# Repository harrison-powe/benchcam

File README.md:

# BenchCam

catching actuators in the act

BenchCam is a **local-first**, bench-side **capture + event-marking workflow**
for documenting hardware work. You start a session, log time-stamped markers as
you work (e.g. "power on", "chip lifted", "fault"), optionally record video with
an **off-the-shelf webcam**, and end up with a self-contained folder of plain
files you can read with any text editor — plus an optional auto-edited review
clip that timelapses the boring parts and slows down around each marker.

> **Status:** v0, now exercised on **real bench sessions**. Two real
> `hello-motion` sessions exist — a connection-debugging session and one where the
> actuator was recorded **spinning on command** (open-loop bring-up, narrated on
> camera). The capture path, the physical **START/MARK/STOP/MUTE** buttons with
> their record/mute LEDs and OLED status panel, and the full post-capture pipeline
> (transcribe → auto-chapter → speech-aware review clip) have all run on real
> footage. Honest caveats: the physical controls still run on the **breadboard**
> rig — a v1 control PCB is built and electrically verified but has **never
> successfully driven anything**
> (see [The v1 control PCB](#the-v1-control-pcb-built-and-verified-not-yet-working)) —
> the actuator sessions were bring-up/debugging rather than a polished showcase,
> and raw capture still records to a **microSD** until the external SSD is
> deployed. Treat it as an early, working tool, not a finished product.

## What BenchCam is (and is not)

- It is a **software workflow**: it records a session, logs markers (events with
  a timestamp + label), and can auto-edit a review clip. Everything is kept in
  local files only — **no cloud sync, no accounts**.
- For video it drives **existing, off-the-shelf tools**: an `ffmpeg` subprocess
  capturing a USB webcam, or OBS Studio over OBS WebSocket. **BenchCam does not
  build, sell, or include any camera, capture card, or hardware** — you supply a
  regular webcam and (optionally) OBS or ffmpeg.
- It is **not** a camera system and **not** a robotics or motion-control system.
  It uses off-the-shelf cameras and compute (a USB webcam, a Raspberry Pi) and
  does **not** build a camera, capture card, image sensor, or high-speed video
  electronics. It **does** have physical controls — tactile START/MARK/STOP/MUTE
  buttons, record/mute status LEDs, and a small I²C status display wired to the
  Pi's GPIO — and it switches **one bench ring light** (an illumination load, through
  a low-side MOSFET) so the light follows the recording. That is the entire extent
  of what it drives: it stays on the **observation** side and **never commands
  actuators or any moving hardware** (it may *receive* external marker events, but
  never commands motion).

v0 ships with a **NullRecorder** (records no video) so you can use and test the
session + marker workflow immediately, with or without a camera. The
**FfmpegRecorder** records real, audio-synced video by driving an external
`ffmpeg`: on **Linux / Raspberry Pi** it captures the webcam over V4L2 and the mic
over ALSA into `capture.mkv` — this is the primary bench setup — and on
**Windows** it captures over DirectShow (see
[Recording video with ffmpeg](#recording-video-with-ffmpeg)). The **ObsRecorder**
drives OBS Studio's recording on Windows (see
[Recording video with OBS](#recording-video-with-obs)).

## How it's deployed (two machines)

In the real bench setup the work is split across two machines:

- **Capture appliance — Raspberry Pi 5 (Linux).** The camera, ring light, and mic
  live at the bench on the Pi. It records over V4L2/ALSA, exposes the physical
  GPIO controls, and runs the dashboard and the button daemon as always-on
  `systemd` services (both survive reboot). Marking a session never needs the
  laptop.
- **Compute / edit / upload — Windows laptop.** Whisper transcription, silero-VAD,
  the `edit` render, and the Claude `label`/`autochapter` API calls run here (on
  the GPU). `benchcam fetch <id>` pulls a session off the Pi over `scp`; only the
  small finished `review.mp4` is uploaded.

The heavy, torch-based extras (`[transcribe]`, `[vad]`) and the `[label]` extra are
**laptop-only** — the Pi install stays stdlib-only so capture has no heavy deps.

### Physical controls (GPIO)

Four tactile buttons, two status LEDs, an I²C status display, and one switched
bench light wire to the Pi's 40-pin header (3.3V logic only):

| Function | GPIO | What it does |
| --- | --- | --- |
| **START** | 27 | create a session and start recording |
| **MARK** | 17 | drop a frame-accurate `source=gpio` marker |
| **STOP** | 22 | stop recording and end the session |
| **MUTE** | 23 | toggle a mute span (force-timelapsed out of the review) |
| record LED | 5 | lit while a session is RUNNING |
| mute LED | 24 | lit while a mute span is open |
| ring light | 6 | bench light through an IRLZ44N low-side MOSFET; on while RUNNING |
| OLED | I²C-1 | SSD1306 128×64 at `0x3C`: elapsed, marker count, mute badge, free space |

The Pi-local daemon [gpio_buttons.py](gpio_buttons.py) debounces the presses and
calls the same session/marker code the CLI uses, so button-driven and CLI-driven
sessions are cross-process safe. It runs as the always-on `benchcam-buttons`
service. Everything below is validated on the **breadboard** rig:

- The **record LED** is derived from the on-disk session state rather than
  in-memory state, so it stays correct across a daemon restart.
- The **status display** shows elapsed time, marker count, a mute badge, and free
  space with a low-space flag — measured against the same pre-flight floor the
  recorder enforces, so the panel can never show a healthy number while START
  would refuse. It refreshes on a background thread, fails soft (no display fault
  can affect capture), and retries a lost panel every 30s.
- **SIGTERM/SIGINT** clears both LEDs and the panel, so a stopped daemon never
  leaves a lit record light or a frozen `●REC` frame on the bench.
- **Mute spans survive a daemon restart** via a session-local sidecar
  (`mute_open.json`) that holds only the currently-open span. `mute_spans.csv`
  itself stays append-only and complete-rows-only, so the renderer never sees a
  half-written span and mistakes it for one running to end-of-session.
- The **ring light** follows the recording through the MOSFET. The circuit is
  validated, but the light currently on the bench has a capacitive touch switch
  that resets on power loss — so the MOSFET can turn it off and never back on.
  Blocked on swapping in a light with a mechanical switch, not on hardware or code.

### The v1 control PCB (built and verified, not yet working)

A single-sided control board was designed and CNC-milled in-house from the KiCad
project in [control-board/](control-board/): 100 × 80 mm FR-1, four buttons,
record/mute LEDs, a 4-pin I²C header for the OLED, an IRLZ44N low-side MOSFET on
a screw terminal for the bench light, and a 2×20 IDC ribbon to the Pi header.
Designed 2026-07-18, milled 07-19, continuity-verified 07-26, fully soldered and
metered 08-02. Because it was milled rather than fabbed, the gerbers and mill
gcode are tracked alongside the design as the reproduction record.

**It has never successfully driven anything.** First bring-up crashed the Pi
twice, and a J1 ground path is intermittent; diagnosis is ongoing. The
**breadboard rig remains the live control surface** for every session.

As-built deltas, recorded so future debugging doesn't chase them:

- **R3 is 220Ω on the board, not the 150Ω in the schematic** (MOSFET gate series
  resistor). The schematic deliberately keeps the designed value.
- A deliberate **solder bridge spans R3 pad 2 to R4 pad 1** — both are already on
  the gate net; it repairs a trace broken during rework. It is a repair, not a
  design change, and a re-mill would not reproduce it.
- **Only the J1 pins that carry a net are soldered** (21 of 40); the other 19 are
  unconnected in the netlist.

## Requirements

- **Python 3.11 or newer** (developed and validated on Python 3.13). The core is
  pure standard library — no third-party packages are required to install or run
  the session/marker workflow or the dashboard.
- For video recording: a working `ffmpeg` binary on your `PATH` (only needed if
  you use `--recorder ffmpeg`; the default `null` recorder needs nothing extra).
- For the OBS recorder: OBS Studio 28+ and the optional `benchcam[obs]` extra
  (only needed if you use `--recorder obs`). See
  [Recording video with OBS](#recording-video-with-obs).
- A regular **USB webcam** if you want video (BenchCam does not provide one).

## Install (Windows / laptop)

The steps below set up the **laptop** (editing, transcription, upload). The
**Raspberry Pi capture box** uses the same editable install on Linux (`pip install
-e .`, no heavy extras) — see
[Recording headless on a Raspberry Pi](#3-recording-headless-on-a-raspberry-pi-linux--v4l2--alsa)
for the capture side.

Open **PowerShell** (or **Command Prompt**) in the project folder.

```powershell
# 1. Create and activate a virtual environment
py -3.11 -m venv .venv
.\.venv\Scripts\Activate.ps1

# 2. Install BenchCam (editable)
pip install -e .
```

If PowerShell blocks the activation script, allow it for the current user:

```powershell
Set-ExecutionPolicy -Scope CurrentUser -ExecutionPolicy RemoteSigned
```

You can also run BenchCam without installing the console script:

```powershell
python -m benchcam --help
```

## Usage (Windows v0)

A session is just four commands. Run them from the same folder so they share the
same `sessions\` directory.

```powershell
# Create a new session (uses the NullRecorder by default)
benchcam new --profile bench-a

# Start the session clock
benchcam run

# Log markers as you work (quote labels that contain spaces)
benchcam mark "power on"
benchcam mark "chip lifted"
benchcam mark "fault observed"

# Close the session
benchcam end
```

### Where sessions are stored

By default session folders are created under `.\sessions\` in the current
directory. To put **all** session data (markers and collected videos) somewhere
else — for example an external SSD — set the `BENCHCAM_SESSIONS_ROOT`
environment variable. Every command honors it, so new sessions and the videos
collected into them land there with no code change and no per-command flag:

```powershell
# Persist it for your user (new shells pick it up automatically):
setx BENCHCAM_SESSIONS_ROOT "E:\benchcam-sessions"

# ...or just for the current shell:
$env:BENCHCAM_SESSIONS_ROOT = "E:\benchcam-sessions"
```

An explicit `--sessions-root PATH` on any command overrides the env var, which
overrides the `.\sessions\` default. No drive letter is hardcoded — point it at
whatever drive you like (the external SSD is the intended home once it's
available).

### Fast marking with `benchcam live`

`new`/`run`/`mark`/`end` each run as a separate process, which is fine for
occasional marks but slow when your hands are busy at the bench. `benchcam live`
opens a single long-running shell that holds the active session in memory and
marks on **one keypress** — no per-mark process startup, no re-reading
`markers.csv`.

```powershell
# Create a session first (if you don't already have an active one)
benchcam new --profile bench-a

# Enter the live shell (starts the session if it hasn't started yet)
benchcam live
```

Inside the shell:

| Key | Action |
| --- | --- |
| `Space` / `Enter` | Mark **now**, no label. Fast path — prints index + elapsed seconds instantly. |
| `l` | Mark now, then type a one-line label (empty label is allowed). |
| `n` | Append a line to `notes.md` (fills the gap where notes were write-once). |
| `s` | Show status: session id, elapsed time, marker count so far. |
| `q` | Quit cleanly: stop the recorder, end the session, print a summary. |

Notes:

- `live` attaches to the same active session as the other commands. If the
  session is still `created`, it starts it (same effect as `run`, including
  `recorder.start`). If it has already `ended`, it refuses with a clear message.
- Every mark is still **appended to `markers.csv` immediately** for crash
  safety; only the next marker index is tracked in memory.
- Markers made here use `source = manual`, exactly like `benchcam mark`.

This produces a folder like:

```
sessions\2026-06-17_05-43-00\
    session.json
    markers.csv
    notes.md
```

### session.json

```json
{
  "session_id": "2026-06-17_05-43-00",
  "created_wall_time": "2026-06-17T05:43:00.123456+00:00",
  "profile": "bench-a",
  "camera": "",
  "microphone": "",
  "recorder": "null",
  "storage_path": "sessions\\2026-06-17_05-43-00",
  "notes": "",
  "status": "ended",
  "started_wall_time": "2026-06-17T05:43:10.000000+00:00",
  "ended_wall_time": "2026-06-17T05:45:00.000000+00:00"
}
```

### markers.csv

```csv
marker_index,elapsed_seconds,wall_time,source,label,narration
1,2.500,2026-06-17T05:43:12.500000+00:00,gpio,Power Connected,so I've got power to the board now
2,15.250,2026-06-17T05:43:25.250000+00:00,manual,chip lifted,
```

- `elapsed_seconds` is measured from when the session started (`benchcam run`).
- `source` records where the marker came from: `manual` (`benchcam mark` or the
  dashboard), `gpio` (a physical button press), or `auto` (proposed by
  `benchcam autochapter`). `gpio`/`manual` are ground truth and win over `auto`
  on conflict.
- `label` is the short on-screen chapter title. `narration` is the raw
  transcribed speech near the marker (written by `benchcam transcribe`), kept in
  its own column so transcription and labeling never clobber each other.

### notes.md

A free-form Markdown file for whatever you want to jot down during the session.

## CLI reference

| Command | What it does |
| --- | --- |
| `benchcam new` | Create a new session folder and make it the active session. |
| `benchcam run` | Start recording / start the session clock. |
| `benchcam mark "label"` | Append a time-stamped marker to the active session. |
| `benchcam live` | Interactive shell that marks the active session on a single keypress. |
| `benchcam end` | Stop recording and close the active session. |
| `benchcam transcribe` | Fill each marker's `narration` from the audio with Whisper *(laptop; `[transcribe]` extra)*. |
| `benchcam label` | Summarize each marker's narration into a terse technical `label` via the Claude API *(laptop; `[label]` extra + `$ANTHROPIC_API_KEY`)*. |
| `benchcam autochapter` | Propose chapters from the **full-session** transcript and write them as `source=auto` markers; merges with real markers, which win *(laptop; `[transcribe]`+`[label]`)*. |
| `benchcam chapters` | Review/re-title chapters without re-watching: print, or `--edit`/`--apply` an editable `chapters.txt` (updates only the `label` column). |
| `benchcam edit` | Render a marker-aware `review.mp4` (timelapse + normal-speed windows + persistent chapter tags). Flags: `--vad`, `--auto`, `--preview`, `--fetch`. |
| `benchcam publish` | Export a paste-ready YouTube chapter block (remapped review timestamps) to `youtube_chapters.txt`. Read-only; never uploads. |
| `benchcam fetch` | Pull a recorded session off the Pi over `scp` to the laptop and open it *(run on the laptop)*. |
| `benchcam dashboard` | Local web UI to run a whole session (start/mark/stop/review) from a browser. |

Useful options:

- `benchcam new --profile NAME --camera DESC --microphone DESC --recorder {null,obs,ffmpeg} --notes "..."`
- `benchcam mark "label" --source external`
- `benchcam edit --session ID --pre 3 --post 5 --speed 30 [--vad] [--auto] [--preview] [--fetch] --font PATH`
- `--sessions-root PATH` (on any command) to use a different sessions directory.

Roughly, a full session flows: **capture** (Pi: `run`/`mark`/`end` or the GPIO
buttons) → **fetch** to the laptop → **transcribe** + **label** *or* **autochapter**
→ **edit** → optionally **chapters** to re-title → **publish** the chapter block.
`benchcam edit --auto` runs the transcribe → autochapter → render chain in one
command, skipping any step whose output already exists.

The "active" session is tracked by a small pointer file at
`sessions\.active`, so `run`, `mark`, and `end` know which session to use.

## Recorders

- **NullRecorder** (`null`, default): records no video. Lets you exercise the
  session and marker workflow, and pairs well with capturing video manually in a
  separate app.
- **ObsRecorder** (`obs`): drives OBS Studio's recording over OBS WebSocket v5
  (optional `benchcam[obs]` extra). See
  [Recording video with OBS](#recording-video-with-obs).
- **FfmpegRecorder** (`ffmpeg`): records one capture file per session by driving
  an external `ffmpeg` binary. Two paths are supported and selected by platform:
  Windows (DirectShow / dshow, video-only `capture.mp4`) and Linux (V4L2 + ALSA,
  `capture.mkv` with audio — e.g. a Raspberry Pi capturing from a C920). See
  [Recording video with ffmpeg](#recording-video-with-ffmpeg).

See `src/benchcam/recorders/` for the recorder code.

## Recording video with ffmpeg

The `ffmpeg` recorder captures one file into the session folder (**`capture.mp4`**
on Windows, **`capture.mkv`** on Linux). It starts when the session starts, so the
video timecode lines up with each marker's `elapsed_seconds`. ffmpeg is run as an
external binary — BenchCam adds no Python ffmpeg dependency, so you must have
`ffmpeg` on your `PATH` (`winget install Gyan.FFmpeg`, or download from
[ffmpeg.org](https://ffmpeg.org/download.html) and add it to `PATH`; on Debian/RPi
OS `sudo apt install ffmpeg`).

### 1. Find your camera's device name

The DirectShow device name (for a Logitech C920S it is usually
`HD Pro Webcam C920S`) must be passed exactly. List the devices on your machine:

```powershell
ffmpeg -list_devices true -f dshow -i dummy
```

Look under "DirectShow video devices" for the quoted name of your webcam.

### 2. Start a session that records from the camera

Pass the device name with `--camera`; it is stored in `session.json` and used as
the source of truth for the device. (You can also set the `BENCHCAM_CAMERA`
environment variable; an explicit `--camera` on the session wins.)

```powershell
benchcam new --recorder ffmpeg --camera "HD Pro Webcam C920S" --profile bench-a
benchcam live
```

`benchcam live` (or `benchcam run`) launches ffmpeg in the background and returns
immediately; quitting `live` (or `benchcam end`) sends `q` to ffmpeg so the MP4
is finalized and playable, force-killing only if it does not exit in time. If
`ffmpeg` is missing from `PATH`, or no camera name is configured, the command
fails with a clear message instead of silently recording nothing.

Defaults are tuned for the C920S: 1080p30 over MJPEG, H.264 (`libx264`), video
only (no audio). An `ffmpeg.log` is written next to the video for troubleshooting.

### 3. Recording headless on a Raspberry Pi (Linux / V4L2 + ALSA)

On Linux the recorder captures over **V4L2** and writes **`capture.mkv`**. The
C920 emits MJPEG natively, so the stream is **copied** (`-c:v copy`) — the Pi
never transcodes — and Matroska is used because MJPEG stream-copy is unreliable
in `.mp4`. ALSA audio (e.g. a Yeti Nano) is muxed into the same file.

The defaults match a confirmed C920 + Yeti Nano setup, so a plain session works
out of the box:

```bash
benchcam new --recorder ffmpeg --profile bench-pi
benchcam run        # captures /dev/video0 (mjpeg 1920x1080@30) + Yeti via ALSA
# ... benchcam mark "label" ...
benchcam end        # sends 'q' so capture.mkv is finalized
```

Everything is configurable (nothing is hardcoded in the command builder):

| Setting        | Default                   | Override |
| -------------- | ------------------------- | -------- |
| Video device   | `/dev/video0`             | `--camera` (stored in session.json) or `BENCHCAM_CAMERA` |
| Audio device   | `plughw:CARD=Nano,DEV=0`  | `--microphone` (stored in session.json) or `BENCHCAM_MICROPHONE` (set empty to disable audio) |
| Input format   | `mjpeg`                   | `BENCHCAM_INPUT_FORMAT` |
| Resolution     | `1920x1080`               | `BENCHCAM_VIDEO_SIZE` (`WxH`) |
| Frame rate     | `30`                      | `BENCHCAM_FRAMERATE` |

Discover V4L2 devices with `v4l2-ctl --list-devices` and ALSA capture devices
with `arecord -L`. The underlying command is equivalent to the manually
validated:

```bash
ffmpeg -f v4l2 -input_format mjpeg -framerate 30 -video_size 1920x1080 \
  -i /dev/video0 -f alsa -ac 2 -ar 44100 -i plughw:CARD=Nano,DEV=0 \
  -c:v copy -c:a aac capture.mkv
```

> Harmless `Dequeued v4l2 buffer contains corrupted data` warnings at stream
> startup are expected; they are logged to `ffmpeg.log` and are not fatal.

> macOS note: the avfoundation input path is still a TODO stub in
> `build_ffmpeg_command`.

## Recording video with OBS

The `obs` recorder lets BenchCam drive **OBS Studio**'s recording over OBS
WebSocket v5. OBS stays your live dashboard (preview, framing, focus) while
BenchCam tells it when to start and stop. Because BenchCam triggers the start,
marker `elapsed_seconds` lines up with the OBS video timecode automatically.

**OBS writes the video to its own configured recording folder** (BenchCam can't
change where OBS records). So when the session ends, BenchCam **collects** that
video — it *moves* the file into the session folder as `capture.<ext>` (the
extension is whatever OBS wrote, `.mkv` or `.mp4`), so the video ends up right
next to `markers.csv` / `session.json` / `notes.md` and each session folder is
self-contained. The `obs_recording.txt` pointer and a `notes.md` line are updated
to the new in-folder path.

If the move can't happen (file still locked, drive missing, etc.), the session
still ends cleanly and the pointer keeps the original OBS path — collection
degrades to "pointer to the external file", never to lost footage. The move is
cross-drive safe (it falls back to copy-then-delete), so it works even when OBS
records on `C:` and your session root is on an external SSD.

> Single-app camera constraint: with the OBS recorder, **OBS owns the camera**
> and provides the live preview. Do not also run the ffmpeg recorder against the
> same C920S — only one app can hold the camera at a time.

### 1. Install OBS and enable the WebSocket server

1. Install OBS Studio 28 or newer (WebSocket v5 is built in — no plugin needed).
2. In OBS: **Tools → WebSocket Server Settings**.
3. Check **Enable WebSocket server**. Note the **Server Port** (default `4455`).
4. Click **Show Connect Info** to see / copy the **Server Password** (auth is on
   by default).

### 2. Install the optional extra and set the password

The OBS client (`obsws-python`) is an **optional** dependency — the core BenchCam
install needs nothing third-party. Install the extra and pass the password via an
environment variable (never commit it):

```powershell
pip install -e ".[obs]"

# Connection config (constructor arg > env vars > defaults). Set at least the
# password; host/port default to localhost/4455.
$env:BENCHCAM_OBS_PASSWORD = "<the password from Show Connect Info>"
# Optional overrides:
# $env:BENCHCAM_OBS_HOST = "localhost"
# $env:BENCHCAM_OBS_PORT = "4455"
```

If `obsws-python` isn't installed, or OBS isn't running / reachable, the `obs`
recorder fails with a clear, actionable error instead of silently recording
nothing.

### 3. Run a session with the OBS recorder

```powershell
benchcam new --recorder obs --profile bench-a
benchcam live
```

Entering `live` (or `benchcam run`) connects to OBS and sends `StartRecord`;
quitting `live` (or `benchcam end`) sends `StopRecord`, captures the file path OBS
wrote, and disconnects. If OBS is *already* recording when you start, BenchCam
refuses (so you don't end up with a second, misaligned recording).

After the session, the OBS video is `sessions\<id>\capture.mkv` (or `.mp4`) next
to `markers.csv`, `obs_recording.txt` records its final path, and the marker
`elapsed_seconds` values map directly onto that recording's timecode.

## Auto-editing a review clip (`benchcam edit`)

`benchcam edit` turns a recorded session into a YouTube-ready "build log"
`review.mp4` with no manual editing:

- The stretches between events are **timelapsed** (default `--speed 30` for 30x).
- Around each marker the clip drops to **normal speed** for a window — default
  `--pre 3` seconds before and `--post 5` seconds after. Overlapping or adjacent
  windows merge into one normal-speed segment.
- With **`--vad`**, actual **speech** (detected by silero-VAD) also drives normal
  speed, so a timelapse never cuts you off mid-sentence and a chapter never flips
  before you start talking. A marker still forces a normal-speed window even when
  silent.
- **MUTE spans** (from `mute_spans.csv`, written by the MUTE button) are
  **force-timelapsed** — the mirror of a marker — even over speech, so asides you
  don't want in the video compress into the montage.
- **Audio** is kept full-precision in the normal-speed windows (your narration)
  and dropped in the timelapsed stretches (no chipmunk audio).
- Each chapter's **label** renders as a persistent on-screen **chapter tag**
  (top-left, monospace) that stays from its marker until the next chapter begins —
  a running "where am I now" indicator, drawn across timelapse segments too, not
  just a brief caption.
- If the capture is **unfinalized/headerless** (a card-full or hard-killed
  session with no duration header), `edit` does a one-time lossless remux to a
  sidecar and proceeds instead of refusing.

It reads the session's `capture.*` and `markers.csv` and writes `review.mp4` into
the **same** session folder. It needs `ffmpeg` (and `ffprobe`, which ships with
ffmpeg) on your `PATH` — see [Recording video with ffmpeg](#recording-video-with-ffmpeg)
for install instructions.

**One-command pipeline.** `benchcam edit --auto` orchestrates full-session
**transcribe → autochapter → render** in a single command, skipping any expensive
step whose output already exists (so re-rendering after a title tweak does zero
Whisper/API work). `--preview` writes a fast 720p `review.preview.mp4` for
iterating on chapter titles without a full render, and `--fetch` pulls the session
from the Pi first. These compose with `--vad`/`--speed`.

```powershell
# Edit the newest session with the defaults (3s pre / 5s post / 30x):
benchcam edit

# ...or a specific session, with custom pacing:
benchcam edit --session 2026-06-18_05-43-00 --pre 2 --post 6 --speed 12

# Custom caption font (optional):
benchcam edit --font "C:\Windows\Fonts\arial.ttf"
```

Chapter tags are rendered by ffmpeg's `drawtext`. BenchCam escapes the text and
the font path for ffmpeg's filtergraph automatically (so Windows paths like
`C:\Windows\Fonts\consola.ttf` and labels containing `:`, `'`, `,`, `\`, or `%`
render correctly), and passes the filtergraph via a temp filterscript. Tags
default to a **monospace** "engineering-terminal" font (Consolas on Windows,
DejaVu Sans Mono on Linux) for the aligned look; if the chosen `--font` isn't
found it falls back to a known system monospace font, and finally to ffmpeg's
default — the render never dies on a missing font. Pass `--font` to override.

`benchcam edit` first prints the **segment plan** (which stretches are timelapsed
vs. normal speed, and which captions land where) so you can sanity-check the
pacing before watching, then renders `sessions\<id>\review.mp4`. Re-running
overwrites `review.mp4` cleanly; `capture.*` is never modified or deleted.

Notes:

- **No markers** → a straight `--speed` timelapse of the whole video (still a
  quick way to skim a session); `edit` says so.
- Marker times past the end of the video are clamped to its length.
- The review is **timelapsed**, so a marker's raw `elapsed_seconds` is **not** its
  timestamp in `review.mp4`. `edit` prints the raw→review time map in its segment
  plan, and `benchcam publish` turns that map into a paste-ready YouTube chapter
  block — don't hand YouTube the raw marker times.
- If `capture.*` is missing (e.g. an OBS session where collection failed and only
  `obs_recording.txt` remains), `edit` follows that pointer to the original file;
  if it still can't be found, it fails with a clear message.

## Web dashboard (run a session without a terminal)

`benchcam dashboard` starts a small **local** web server (stdlib `http.server`,
bound to `127.0.0.1:8765`, no accounts, no external exposure) and opens your
browser to a one-page UI. From there you can start a session, mark events (click
or labeled), add notes, stop, and render the review clip — without typing any
terminal commands.

```powershell
benchcam dashboard
```

The page has a clear **● RECORDING / ○ IDLE** indicator so you always know the
state, a big **MARK** button (plus a label field), a notes field, **Stop**, and a
**Session library** with per-session actions. It calls the same BenchCam logic as
the CLI — start = `new` + `run`, mark = `mark`, stop = recorder stop + collect +
`end`, review = `edit`. If OBS isn't running, starting an OBS session shows a
clear error rather than silently failing; a second start is refused; stopping
when nothing is active is a no-op with a message.

**Naming sessions:** the Start screen has an optional **Session name** field.
When set, the session folder becomes `<timestamp>_<slug>` (e.g.
`2026-06-18_14-41-31_moteus-first-spin`) — the timestamp prefix is kept for
sorting/uniqueness — and the friendly name is stored in `session.json` so the UI
shows it nicely. With no name, the folder is timestamp-only as before; older
sessions without a name fall back to showing their folder name.

**Session library:** a list of every session under the sessions root (newest
first) showing the name, date/time, marker count, length, and whether a
`review.mp4` exists. Per row you can **Open video** (the capture in your default
player), **Make review** / **Open review** (render with the `pre`/`post`/`speed`
controls, or open the existing one), **Open folder** (in the file explorer), and
rename the session inline. Renaming an **ended** session **renames the folder on
disk** to `<original-timestamp>_<new-slug>` (the timestamp prefix is kept) and
updates `session.json` (and repoints `obs_recording.txt`/`.active` if needed), so
File Explorer reflects the new name. The currently recording session can't be
renamed — stop it first. The library just scans the session folders — there's no
separate database.

> The dashboard's MARK button is a click convenience. For hands-busy marking,
> `benchcam live` in a terminal (single keypress per marker) is still the fastest
> path — the dashboard does not replace it.

With the OBS recorder, **OBS itself is your live camera preview** next to the
dashboard; BenchCam just drives OBS's record start/stop so markers stay aligned.

The recorder dropdown defaults to the sensible choice for the machine: **ffmpeg**
on Linux (the Raspberry Pi capture box) and **OBS** on Windows — so you don't
have to pick it from the dropdown every time. Every recorder is still selectable.

### Use it from your phone (LAN access)

By default the dashboard binds to `127.0.0.1`, so it's reachable only from the
machine it runs on. To open it from a **phone on the same Wi-Fi** (e.g. standing
at the bench by the Pi), bind it to the LAN — this is **opt-in** because the
dashboard has **no authentication**:

```bash
# On the Pi (headless): expose on the LAN, don't try to open a local browser.
benchcam dashboard --lan --no-browser
# Equivalent: benchcam dashboard --host 0.0.0.0
# Or set it once:  export BENCHCAM_DASHBOARD_HOST=0.0.0.0
```

On startup it prints the actual phone-reachable URLs (the Pi's LAN IP and its
`http://<hostname>.local:8765/` mDNS name) — open one of those on your phone. It
never prints the bare `0.0.0.0` wildcard. **Only enable LAN access on a network
you trust**, since anyone on that network can reach the (unauthenticated) UI.

### OBS password (no env var needed)

You don't need to set `BENCHCAM_OBS_PASSWORD` before launching. When the OBS
recorder is selected, the Start screen shows an **OBS WebSocket password** field
(and optional host/port). Enter the password from OBS's **Tools → WebSocket
Server Settings → Show Connect Info** once and start a session — BenchCam saves
it to a **local, git-ignored** file at `.benchcam\config.json` (under the project
folder), so you won't have to re-enter it on future launches (leave the field
blank to reuse the saved one). The password resolves in order:

1. the field you typed on the Start screen,
2. the saved `.benchcam\config.json`,
3. the `BENCHCAM_OBS_PASSWORD` environment variable,

and if none is available the start fails with the same clear "authentication
enabled but no password provided" error as the CLI. The `.benchcam\` folder (and
`.env`) are git-ignored, so the password is never committed. Host/port work the
same way (defaulting to `localhost:4455`).

### Launcher with no console window (recommended)

For a clean double-click that just opens the dashboard — **no console window,
no flash** — use `scripts\benchcam-dashboard.vbs`. It runs `benchcam dashboard`
with the venv's `pythonw.exe` (the windowless Python), so nothing visible appears
while the server runs in the background for your session.

**Desktop shortcut (a):**

1. In File Explorer, open the project's `scripts\` folder.
2. Right-click **`benchcam-dashboard.vbs`** → **Show more options** → **Send to**
   → **Desktop (create shortcut)**. Double-clicking it now opens the dashboard
   with no console window.

**Pin to the taskbar (b):** A shortcut to a `.vbs` can't be pinned directly, but
a shortcut to **`wscript.exe`** can (it's an `.exe`). So point the shortcut at
`wscript.exe` and pass the script as an argument:

1. Right-click the desktop → **New → Shortcut**.
2. For the location, enter (use YOUR full path to the repo):

   ```text
   wscript.exe "C:\path\to\benchcam\scripts\benchcam-dashboard.vbs"
   ```

3. Name it **BenchCam**, finish, then right-click it → **Pin to taskbar**
   (or **Pin to Start**). Because the target is `wscript.exe`, pinning is allowed.

**Custom icon (c):** Right-click the shortcut → **Properties** → **Change
Icon…** → browse to your `.ico` → **OK**. The icon shows on the desktop shortcut
and on the pinned taskbar button.

**Stopping it:** because there's no window, stop the dashboard from **Task
Manager** → end the background **`pythonw.exe`** process running BenchCam (or just
leave it; it's a tiny local server). If a double-click seems to do nothing, the
dashboard is probably already running — open <http://127.0.0.1:8765> in your
browser, or stop the existing `pythonw.exe` first.

> The launcher assumes a `.venv` in the project root with BenchCam installed
> (`py -3 -m venv .venv` → activate → `pip install -e .`, plus
> `pip install -e ".[obs]"` if you use the OBS recorder).

### Alternative launcher: the `.bat` (shows a console)

`scripts\benchcam-dashboard.bat` (and the PowerShell `scripts\benchcam-dashboard.ps1`)
activate the venv and run `benchcam dashboard` too, but they keep a **console
window** open (closing it stops the dashboard, which is handy). To use it: open
`scripts\`, right-click **`benchcam-dashboard.bat`** → **Send to → Desktop
(create shortcut)**, and optionally set the shortcut's **Run:** to **Minimized**.
Prefer the `.vbs` launcher above for a no-console, pinnable experience.

### Run a full session from the dashboard

1. (OBS recorder) Open OBS with your C920S as a source so you have a live
   preview, and make sure its WebSocket server is enabled (see
   [Recording video with OBS](#recording-video-with-obs)).
2. Double-click the desktop shortcut → the dashboard opens in your browser.
3. Pick the recorder (OBS by default), optionally type a profile and a
   **Session name**, and — the first time — paste the OBS WebSocket password into
   the **OBS WebSocket password** field (it's saved locally afterward). Click
   **Start session**; the indicator turns red **● RECORDING**.
4. Work at the bench: click **MARK now** for quick markers, or type a label and
   click **Mark + label**; add free-form notes with the note field. Markers
   appear in the live list with their elapsed time.
5. Click **Stop session** → the indicator returns to **○ IDLE** and the session
   appears at the top of the **Session library**.
6. In the library row, click **Make review** → BenchCam renders the marker-aware
   review clip into the session folder, opens it, and the row flips to **Open
   review** for next time. **Open video** plays the raw capture.

### 30-second manual test (Windows 11)

From the project folder, in PowerShell, with BenchCam installed:

```powershell
benchcam new --profile quicktest
benchcam live
```

Then, inside the live shell:

1. Press `Space` twice — you should see `marker #1` and `marker #2` with elapsed
   seconds.
2. Press `l`, type `chip lifted`, press `Enter` — you should see `marker #3 ... chip lifted`.
3. Press `n`, type `looks good`, press `Enter` — confirms a note was appended.
4. Press `s` — prints the session id, elapsed time, and `markers 3`.
5. Press `q` — prints a summary and exits.

Finally, open the newest folder under `sessions\` and confirm `markers.csv` has
three rows (two blank labels, one `chip lifted`) and `notes.md` ends with
`looks good`.

## Development

```powershell
pip install -e ".[dev]"
pytest
```

## Data and privacy

- BenchCam writes only to your local `sessions\` directory.
- Video/media files (each session's `capture.mp4`/`capture.mkv`, whether written
  by ffmpeg or collected from OBS) and the `sessions\` directory are
  **git-ignored** and must not be committed. Video is large — keep recordings on
  your external SSD (set `BENCHCAM_SESSIONS_ROOT`), not in git.

## Project layout

```
src/benchcam/
    cli.py            argparse CLI (new/run/mark/live/end/edit/transcribe/
                      label/autochapter/chapters/publish/fetch/dashboard)
    session.py        session model + on-disk layout
    markers.py        markers.csv reading/writing (incl. the narration column)
    live.py           interactive single-keypress marking shell
    keypress.py       cross-platform single-key reader (msvcrt / termios)
    transcribe.py     Whisper narration -> the marker `narration` column ([transcribe])
    label.py          narration -> terse technical label via the Claude API ([label])
    autochapter.py    full-session transcript -> faithful source=auto chapters
    chapters.py       review / re-title chapters (chapters.txt) without re-watching
    editor.py         marker-aware auto-edit -> review.mp4 (timelapse, VAD, chapter tags)
    publish.py        export a YouTube chapter block from the review remap
    dashboard.py      local web UI (stdlib http.server) over the existing logic
    config.py         local gitignored config (.benchcam/config.json; OBS creds)
    clock.py          time helpers
    recorders/
        base.py       Recorder interface
        null.py       NullRecorder (default)
        obs.py        ObsRecorder (OBS Studio via OBS WebSocket v5)
        ffmpeg.py     FfmpegRecorder (ffmpeg subprocess; Linux V4L2/ALSA + Windows dshow)
        collect.py    move an external recording into the session folder
scripts/
    benchcam-dashboard.vbs   no-console Windows launcher (recommended; pinnable)
    benchcam-dashboard.bat   Windows launcher (keeps a console window)
    benchcam-dashboard.ps1   PowerShell launcher
control-board/        v1 control PCB: KiCad source + the gerbers/mill gcode it
                      was cut from (built and verified, NOT yet working)
gpio_buttons.py       Pi-only GPIO daemon: buttons, record/mute LEDs, OLED
                      status panel, mute spans, ring light
reviewer.py           laptop review hub (list / open / watch / make-review)
tests/                unit tests
```

## License

[MIT](LICENSE) © 2026 Harrison Powe.

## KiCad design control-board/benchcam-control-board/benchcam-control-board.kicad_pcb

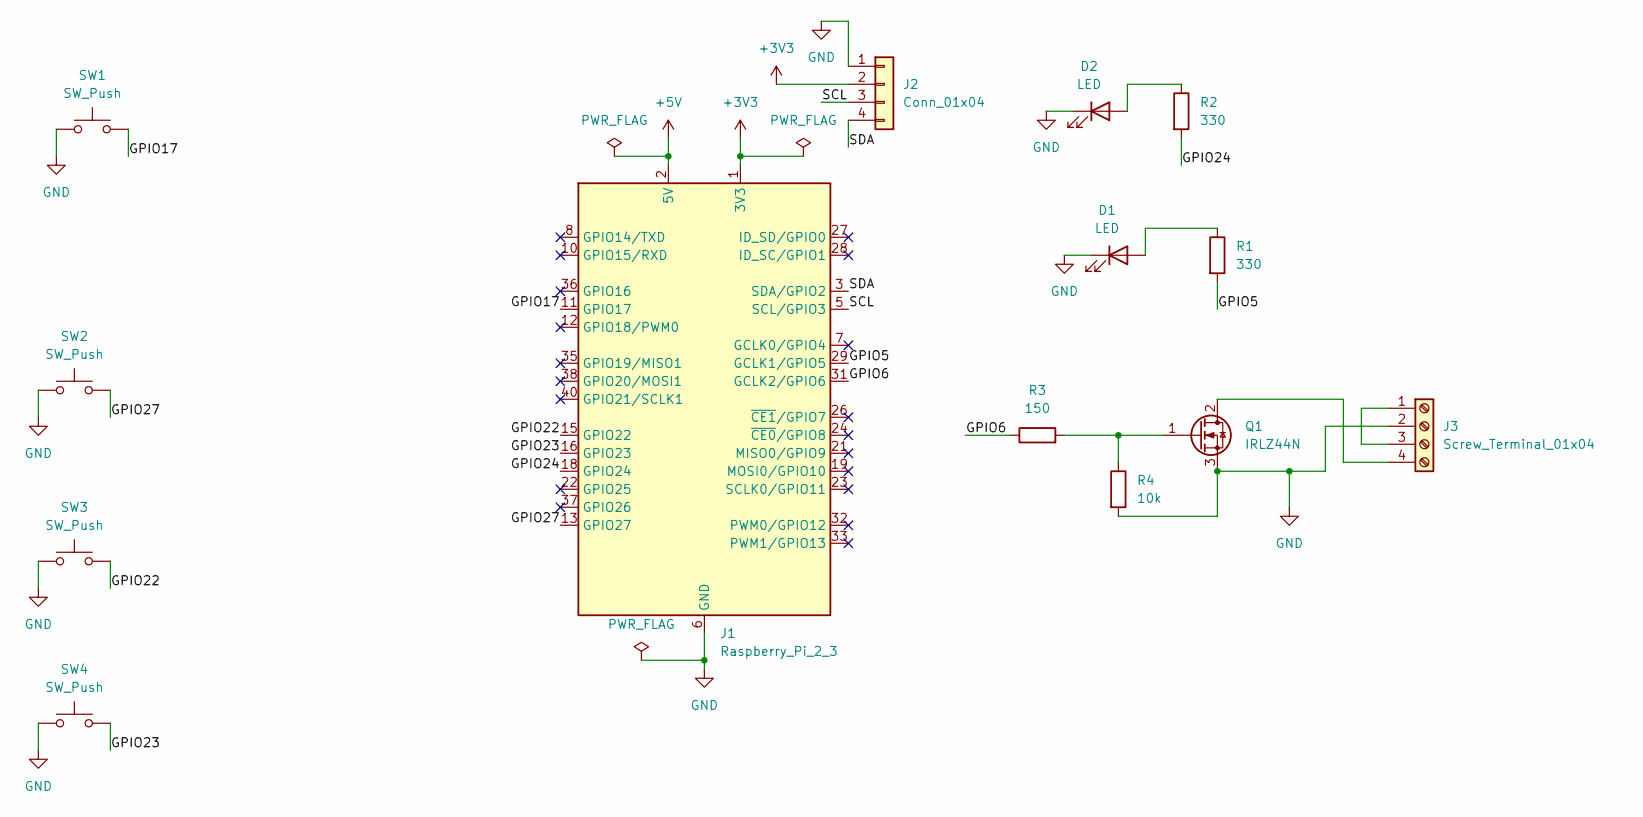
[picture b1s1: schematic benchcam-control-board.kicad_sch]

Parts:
D1, D2: LED; LED_D5.0mm
J1: Raspberry_Pi_2_3; PinHeader_2x20_P2.54mm_Vertical
J2: Conn_01x04; PinHeader_1x04_P2.54mm_Vertical
J3: Screw_Terminal_01x04; TerminalBlock_Phoenix_MKDS-1,5-4-5.08_1x04_P5.08mm_Horizont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
Q1: IRLZ44N; TO-220-3_Vertical
R1, R2: 330; R_Axial_DIN0207_L6.3mm_D2.5mm_P7.62mm_Horizontal
R3: 150; R_Axial_DIN0207_L6.3mm_D2.5mm_P7.62mm_Horizontal
R4: 10k; R_Axial_DIN0207_L6.3mm_D2.5mm_P7.62mm_Horizontal
SW1, SW2, SW3, SW4: SW_Push; SW_PUSH-12mm_Wuerth-430476085716

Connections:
+3V3: J1.1 (3V3), J1.17 (3V3), J2.2
+5V: J1.2 (5V), J1.4 (5V)
/GPIO5: J1.29 (GCLK1/GPIO5), R1.2
/GPIO6: J1.31 (GCLK2/GPIO6), R3.1
/GPIO17: J1.11 (GPIO17), SW1.2
/GPIO22: J1.15 (GPIO22), SW3.2
/GPIO23: J1.16 (GPIO23), SW4.2
/GPIO24: J1.18 (GPIO24), R2.2
/GPIO27: J1.13 (GPIO27), SW2.2
/SCL: J1.5 (SCL/GPIO3), J2.3
/SDA: J1.3 (SDA/GPIO2), J2.4
GND: D1.1 (K), D2.1 (K), J1.6 (GND), J1.9 (GND), J1.14 (GND), J1.20 (GND), J1.25 (GND), J1.30 (GND), J1.34 (GND), J1.39 (GND), J2.1, J3.2, Q1.3 (S), R4.2, SW1.1, SW2.1, SW3.1, SW4.1
unnamed: D1.2 (A), R1.1
unnamed: D2.2 (A), R2.1
unnamed: J3.1, J3.3
unnamed: J3.4, Q1.2 (D)
unnamed: Q1.1 (G), R3.2, R4.1

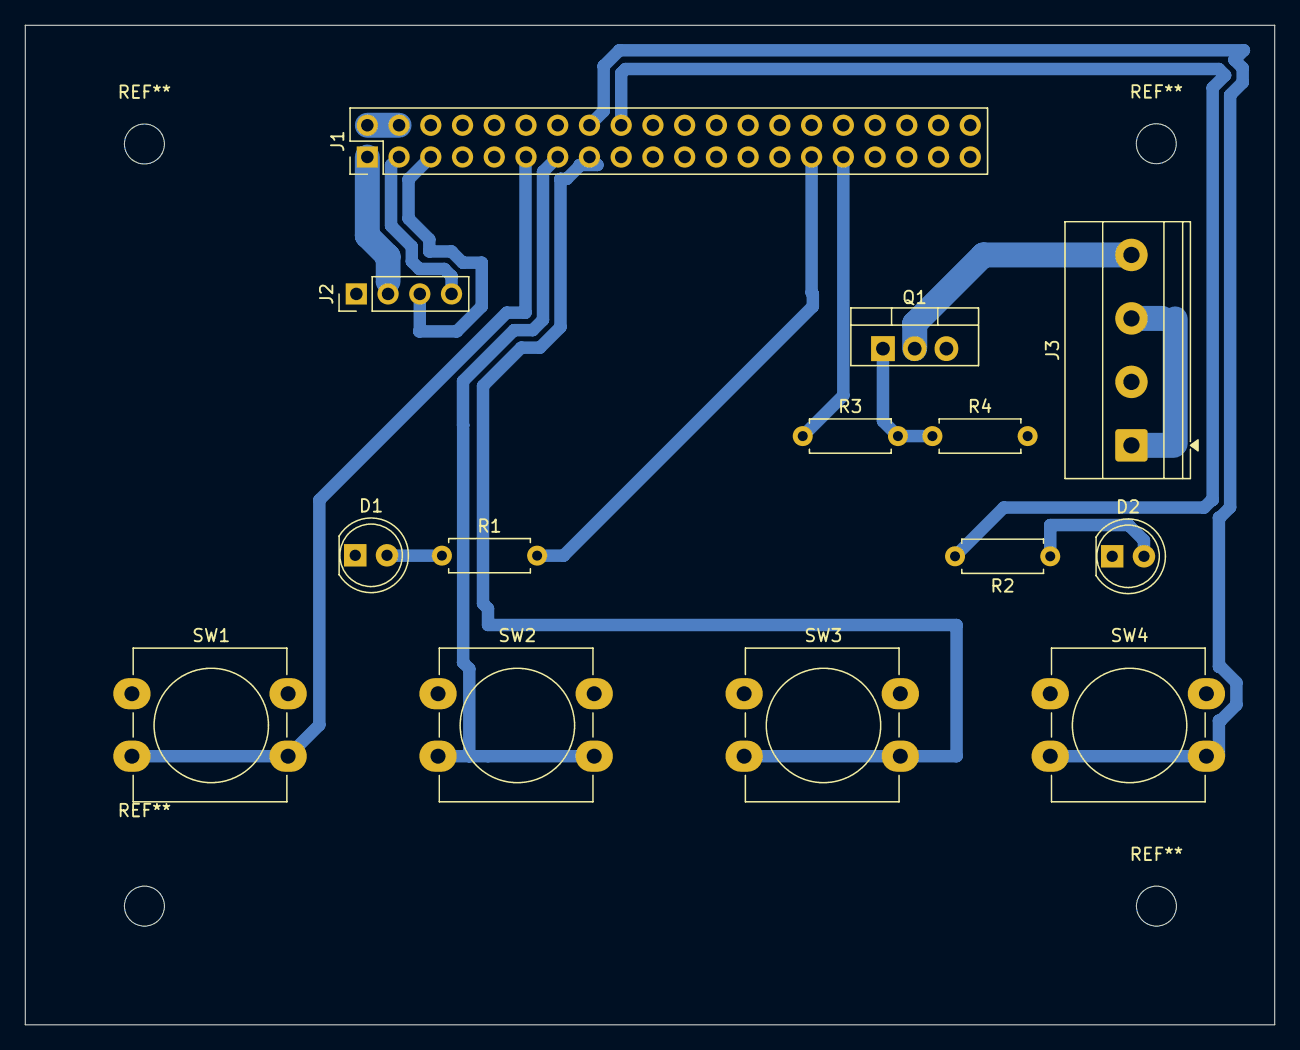
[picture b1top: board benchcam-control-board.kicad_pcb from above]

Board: 2 copper layers, 100.0 x 80.0 mm, 14 parts (0 on the bottom side), 17 nets.

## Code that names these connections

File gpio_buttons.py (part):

#!/usr/bin/env python3
"""BenchCam GPIO control daemon (Pi-only): four physical buttons + two status LEDs.
  START GPIO27 -> create session + start recording (writes ffmpeg.pid)
  MARK  GPIO17 -> drop a gpio marker into the running session
  STOP  GPIO22 -> stop recording (kills ffmpeg via pidfile) + end session
  MUTE  GPIO23 -> toggle a "mute span" (force-timelapse region); LED ON while muted
  LED   GPIO24 -> mute status LED: ON while a mute span is open, OFF otherwise
  LED   GPIO5  -> record status LED: ON while a session is RUNNING, OFF otherwise
  LIGHT GPIO6  -> bench ring light via an IRLZ44N low-side MOSFET; ON while a
                  session is RUNNING. An illumination LOAD, not an indicator —
                  see _shutdown for why it is not cleared on stop.
  OLED  I2C-1  -> SSD1306 128x64 at 0x3C (J2): elapsed, marks, state, free space
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mute_btn  = Button(23, pull_up=True, bounce_time=0.05)
status_led = LED(24)
# ACTIVE-HIGH to match the as-built v1 control PCB: D1 is hardwired
# GPIO5 -> R1(330R) -> anode, cathode -> GND. Do NOT add active_high=False — it
# would invert D1 once the ribbon moves to the board.
# v2 item: GPIO5 defaults to an internal pull-UP (BCM 0-8 do; 9-27 pull down),
# so the pin floats high at boot and during the ~3s systemd RestartSec window —
# roughly 30uA through D1, a very faint glow before the daemon claims the pin as
# an output. Accepted property of the v1 hardware; not worked around in code.
record_led = LED(5)
# Bench ring light, switched by an IRLZ44N low-side N-channel MOSFET: GPIO6 ->
# gate, 10k gate pulldown to GND (holds the gate low through boot, so the light
# is off before this daemon claims the pin — measured: GPIO6 idles `ip pn | lo`,
# no internal pull fighting the pulldown). Active-high is correct here: pin high
# -> gate high -> FET conducts -> light on. initial_value=False (the default)
# drives the gate low at construction, so claiming the pin never flashes it.
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
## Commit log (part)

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2026-06-17 Add BenchCam v0: CLI, sessions, markers, recorders, tests
2026-06-17 Fix capitalization in README subtitle
2026-06-17 harden v0 marker notes and session status
2026-06-17 add interactive keyboard marker mode
2026-06-17 add manual media attachment workflow
2026-06-17 add session review markdown export
2026-06-18 Add interactive 'benchcam live' shell for fast single-keypress marking
    Adds an additive 'live' subcommand: a long-running foreground shell that holds
    the active session in memory and marks on a single keypress, avoiding the
    per-mark process startup + full markers.csv re-read of 'benchcam mark'.
    - keypress.py: cross-platform, injectable single-key reader (msvcrt / termios,
    with a non-TTY stdin fallback), stdlib only.
    - live.py: marking loop. Loads next index once, increments in memory, but still
2026-06-18 Implement FfmpegRecorder: real webcam capture via ffmpeg subprocess
    Replaces the ffmpeg stub with a working recorder that drives an external
    ffmpeg binary (no Python ffmpeg dependency; runtime stays stdlib only) to
    write one playable, marker-aligned video per session.
    - build_ffmpeg_command(): pure, testable arg builder. Windows/dshow target
    (1080p30 MJPEG -> H.264, video only) with device name + output path injected;
    Linux (v4l2) and macOS (avfoundation) are clearly-marked TODO stubs.
2026-06-18 Implement ObsRecorder: drive OBS Studio recording over OBS WebSocket v5
    Replaces the obs stub with a working recorder that tells OBS when to start/stop
    recording, so marker elapsed_seconds aligns with the OBS video timecode. OBS
    stays the live dashboard; BenchCam only controls record start/stop.
    - obs.py: connects via obsws-python's ReqClient, verifies with GetVersion,
    checks GetRecordStatus (refuses if OBS is already recording so timecodes stay
    aligned), then StartRecord. stop() sends StopRecord, captures the returned
2026-06-18 Collect OBS video into the session folder on session end
    The OBS recorder makes OBS write video to its own folder; previously BenchCam
    only saved a pointer (obs_recording.txt). Now, on session end, BenchCam moves
    that video into the session folder as capture.<ext> so each session folder is
    self-contained (video next to markers.csv / session.json / notes.md).
    - recorders/collect.py (stdlib only): collect_recording() moves an external file
    into the session folder, preserving the extension as capture<ext>. Waits
2026-06-18 Fix collect delete-race: retry deleting the original after copy
    When collect falls back to copy+delete across drives, the writer (OBS) often
    still holds the source handle for a moment after StopRecord, so deleting the
    original failed and a duplicate piled up in OBS's folder every session.
    Now the original-delete is retried (default 5 attempts over ~2s) to give the
    handle time to release. Only after the retries are exhausted does it fall back
    to the previous behavior: keep the original, log a warning, never crash, never
2026-06-18 Add marker-aware auto-edit: 'benchcam edit' -> review.mp4
    New 'benchcam edit [--session]' command renders a YouTube-ready build-log clip
    from a session's capture.* + markers.csv into review.mp4, with no manual editing.
    - editor.py (stdlib only for the tested parts; ffmpeg is an external binary):
    * build_segment_plan(): pure segment planner. Each marker gets a normal-speed
    window [t-pre, t+post] (default 3s/5s) clamped to the video; overlapping or
    adjacent windows merge; gaps are timelapsed at --speed (default 8x); no
2026-06-18 Fix drawtext caption/font escaping for Windows ffmpeg render
    The edit command built a correct segment plan but the render died on Windows
    ('No option name near .../arial.ttf', 'Invalid argument') because the drawtext
    fontfile path and caption text were not escaped for ffmpeg's two-level
    filtergraph parser (the drive-letter colon and backslashes in C:\Windows\Fonts\
    arial.ttf, and special chars in marker labels, broke the parse).
    - _escape_fontfile(): backslashes -> forward slashes and the colon escaped as
2026-06-18 Add local web dashboard: run a full session from a browser
    New 'benchcam dashboard' command starts a small stdlib http.server on
    127.0.0.1:8765 and opens the browser to a one-page UI, so a whole session
    (start -> mark -> stop -> review) can be run without touching a terminal. It is
    additive UI over the existing logic and reuses it directly:
    start -> session.create_session + recorder.start + session.start_session
    mark -> session.add_marker
2026-06-18 Dashboard: enter + persist OBS password in the browser (no env var needed)
    Launching the dashboard from a desktop shortcut had no BENCHCAM_OBS_PASSWORD in
    its environment, so OBS start failed with 'authentication enabled but no password
    provided', and setting the env var first defeats the no-terminal goal.
    Now the OBS connection settings can be entered in the browser and are persisted
    locally, with no global env var and no change to the recorder logic or schema:
    - config.py (stdlib only): load/save .benchcam/config.json under the launch
2026-06-18 Add no-console, pinnable Windows launcher for the dashboard
    The .bat launcher flashes/keeps a console window and a .bat shortcut can't be
    pinned to the taskbar. Add scripts/benchcam-dashboard.vbs: it runs
    'benchcam dashboard' via the venv's pythonw.exe (the windowless Python) with a
    hidden, non-blocking WScript.Shell.Run, so there is ZERO console window while the
    server keeps running in the background for the session.
    - It auto-discovers the repo root (parent of scripts\) and the venv pythonw,
2026-06-18 dashboard: fix stop (POST), label markers after marking, keyboard shortcuts
    BUG 1 (Stop didn't stop OBS): the page's Stop button called the JSON helper
    without a body, which made it issue a GET to /api/stop; the server only routes
    that path on POST, so it 404'd and recorder.stop()/StopRecord never ran — OBS
    kept recording and the elapsed timer kept counting.
    - JS now POSTs /api/stop (verified: GET /api/stop -> 404, POST -> stops). After
    stop the UI leaves RECORDING (poll returns active:false: timer stops, indicator
2026-06-18 dashboard: 5 UX polish fixes (password reuse, note blur, in-page stop confirm, auto-open review)
    FIX 1 — OBS password truly persists: the config root defaulted to Path.cwd(),
    so a saved password looked 'forgotten' when the dashboard was launched from a
    different working directory. config.default_config_root() now anchors
    .benchcam/config.json to a STABLE, cwd-independent location (the repo root for an
    editable install, else the home dir), and DashboardController uses it. Saved
    password is reused silently when the field is left blank; the field shows
2026-06-18 dashboard: idempotent launch + hide OBS password field when saved
    CLEANUP 1 — reuse a running dashboard instead of spawning duplicates: launching
    repeatedly piled up idle pythonw.exe servers. serve() now probes the port first
    via is_dashboard_running() (GET /api/status, confirming the BenchCamDashboard
    Server header); if one is already serving it just opens the browser to it and
    returns, starting a new server only when none is running. This holds for both
    'benchcam dashboard' and the .vbs launcher (both go through serve()).
2026-06-18 dashboard: session library with named, browsable sessions + per-session actions
    FEATURE A — named sessions: create_session() takes an optional name; the folder
    becomes <timestamp>_<slug> (slugify: lowercase, spaces->hyphens, strip unsafe
    chars; empty slug -> timestamp-only as before). The human-readable name is stored
    in a new session.json 'name' field; Session.display_name falls back to the folder
    name for older sessions (from_dict ignores unknown/missing fields, so old sessions
    load fine). markers.csv format and the recorder interface are unchanged.
2026-06-18 dashboard: open exactly one browser tab per launch (de-dup + debounce)
    A single launch could end up opening two browser tabs. The browser open is now
    funneled through one place and debounced across processes so a launch results in
    at most one new tab.
    - All browser opening goes through a single open_dashboard_once(url, port) helper
    (the only webbrowser.open call site), used by both serve() paths — so the
    already-running (reuse) path and the fresh-start path can never both open, and
2026-06-18 dashboard: rename a session's FOLDER (up-front naming + rename-later)
    PART 1 (named folder at start) already worked end to end via create_session(name=)
    and the dashboard's Session name field (folder = <timestamp>_<slug>, name stored
    in session.json); added a confirming test.
    PART 2 — rename an ended session's folder on disk:
    - session.rename_session(folder, new_name): renames the folder to
    <original-timestamp>_<new-slug>, KEEPING the timestamp prefix (regenerated from
2026-06-18 dashboard: harden inline rename to single folder-renaming path + HTTP test
    The inline session-name editor already POSTs /api/rename -> rename_session()
    (which moves the folder on disk), but the row handlers could double-fire and
    kept a stale session_id in their closure, so a second request hit the
    now-renamed folder and subsequent row actions (Open folder/video, Make review)
    could target the old path.
    - Inline editor now saves once (Enter -> blur -> change), guarded against a
2026-06-19 Add MIT LICENSE file; align project author/copyright
    - Add a standard MIT LICENSE (2026, Harrison Powe) matching pyproject's
    declared MIT license.
    - Set pyproject authors to 'Harrison Powe' so package metadata and the
    LICENSE copyright holder agree.
2026-06-19 README: honest public framing + status, requirements, license link
    - Reframe the intro as a capture + event-marking *workflow* for documenting
    hardware work, using off-the-shelf tools.
    - Sharpen 'What BenchCam is (and is not)': it's software only, drives an
    off-the-shelf webcam via ffmpeg/OBS, and is NOT a camera system, robotics,
    PCB/firmware, or any physical hardware (no custom controls, no actuators).
    - Add a 'Status: v0, validated on real hardware (desk); not yet used in a real
2026-06-22 Add Linux V4L2+ALSA capture path for headless Pi recording
2026-06-22 Add Linux V4L2+ALSA capture path for headless Pi recording (#18)
2026-06-22 WIP: Linux SIGTERM/SIGKILL stop logic (incomplete - needs PID persistence)
2026-06-22 Persist ffmpeg PID to session folder so cross-process 'end' can stop capture
2026-06-22 fix linux stop (#19)
    * WIP: Linux SIGTERM/SIGKILL stop logic (incomplete - needs PID persistence)
    * Persist ffmpeg PID to session folder so cross-process 'end' can stop capture
2026-06-23 Add Whisper transcribe command to auto-label markers from session audio
2026-06-23 Add Whisper transcribe command to auto-label markers from session audio (#20)
2026-06-23 Add LAN-accessible dashboard with platform-default recorder
2026-06-23 Add LAN-accessible dashboard with platform-default recorder (#21)
2026-06-23 Block heavy review render on the Pi; direct users to render on the laptop
2026-06-23 Block heavy review render on the Pi; direct users to render on the laptop (#22)
2026-06-24 Add laptop-side 'fetch' to pull a session from the Pi and open it
2026-06-24 Add laptop reviewer dashboard (list/open/watch/review, styled)
